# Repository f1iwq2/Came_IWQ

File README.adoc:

Carte CAME-IWQ
==============

Carte de remplacement pour portail coulissants CAME
ZBX6N/7N - A base d'arduino nano
Documents dans le fichier pdf
Fichiers schéma Kicad
fichiers gerber dans le répertoire trace

Replacement control board for CAME sliding gates
Documents in pdf files
Kicad board schematics files
gerber files in trace directory

https://youtu.be/OYu1DCdmt-g

image::clone_came.jpg[]

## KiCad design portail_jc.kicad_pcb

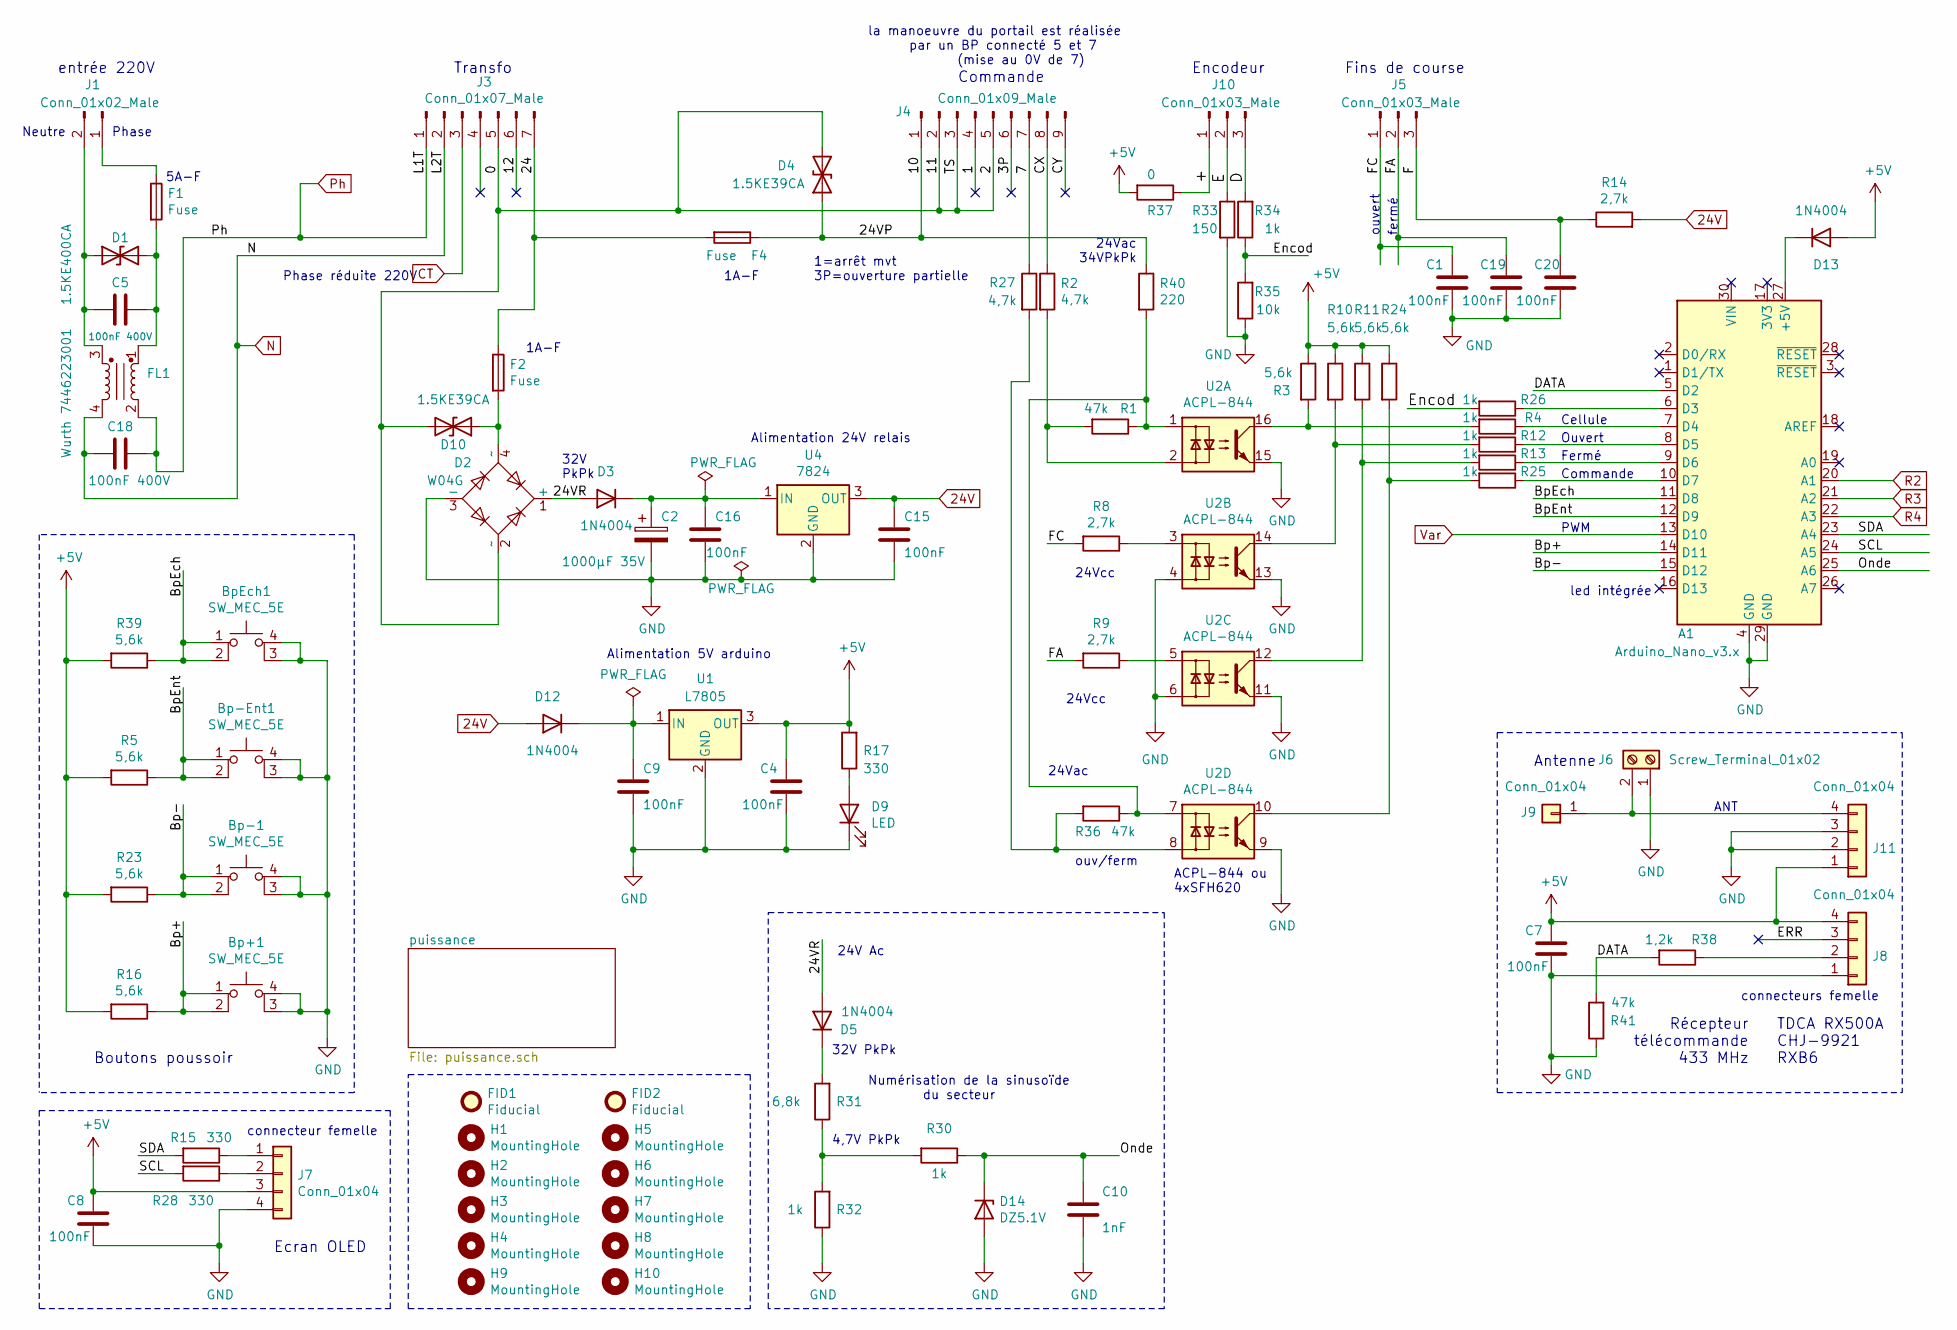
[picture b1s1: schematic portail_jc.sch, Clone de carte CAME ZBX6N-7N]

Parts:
A1: Arduino_Nano_v3.x; Arduino_Nano
Bp+1: SW_MEC_5E; SW_SPST_Omron_B3FS-101xP
Bp-1: SW_MEC_5E; SW_SPST_Omron_B3FS-101xP
Bp-Ent1: SW_MEC_5E; SW_SPST_Omron_B3FS-101xP
BpEch1: SW_MEC_5E; SW_SPST_Omron_B3FS-101xP
C1, C4, C7, C8, C9, C15, C16, C19, C20: 100nF; C_Rect_L7.2mm_W2.5mm_P5.00mm_FKS2_FKP2_MKS2_MKP2
C2: 1000µF 35V; CP_Radial_D12.5mm_P5.00mm
C5, C18: 100nF 400V; C_Rect_L16.5mm_W6.0mm_P15.00mm_MKT
C10: 1nF; C_Rect_L7.2mm_W2.5mm_P5.00mm_FKS2_FKP2_MKS2_MKP2
D1: 1.5KE400CA; R_Axial_DIN0414_L11.9mm_D4.5mm_P15.24mm_Horizontal
D2: W04G; Diode_Bridge_Round_D8.9mm
D3, D5, D12, D13: 1N4004; D_DO-41_SOD81_P10.16mm_Horizontal
D4, D10: 1.5KE39CA; R_Axial_DIN0414_L11.9mm_D4.5mm_P15.24mm_Horizontal
D9: LED; LED_D3.0mm
D14: DZ5.1V; D_A-405_P7.62mm_Horizontal
F1, F2, F4: Fuse; Fuseholder_Cylinder-5x20mm_Schurter_0031_8201_Horizontal_Op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
FID1: Fiducial; KiCad-Logo2_6mm_SilkScreen
FID2: Fiducial; OSHW-Logo2_9.8x8mm_SilkScreen
FL1: Wurth 7446223001; Filtre_wurth
H1, H2, H3, H4: MountingHole; MountingHole_3.2mm_M3
H5, H6, H7, H8: MountingHole; MountingHole_6.4mm_M6
H9, H10: MountingHole; MountingHole_2.7mm_M2.5
J1: Conn_01x02_Male; PhoenixContact_MSTBVA_2,5_2-G-5,08_1x02_P5.08mm_Vertical
J3: Conn_01x07_Male; PhoenixContact_MSTBVA_2,5_7-G-5,08_1x07_P5.08mm_Vertical
J4: Conn_01x09_Male; PhoenixContact_MSTBVA_2,5_9-G-5,08_1x09_P5.08mm_Vertical
J5, J10: Conn_01x03_Male; PhoenixContact_MSTBVA_2,5_3-G-5,08_1x03_P5.08mm_Vertical
J6: Screw_Terminal_01x02; TerminalBlock_bornier-2_P5.08mm
J7, J8, J11: Conn_01x04; PinSocket_1x04_P2.54mm_Vertical
J9: Conn_01x04; PinHeader_1x01_P2.54mm_Vertical
R1, R36, R41: 47k; R_Axial_DIN0207_L6.3mm_D2.5mm_P7.62mm_Horizontal
R2, R27: 4,7k; R_Axial_DIN0207_L6.3mm_D2.5mm_P7.62mm_Horizontal
R3, R5, R10, R11, R16, R23, R24, R39: 5,6k; R_Axial_DIN0207_L6.3mm_D2.5mm_P7.62mm_Horizontal
R4, R12, R13, R25, R26, R30, R32, R34: 1k; R_Axial_DIN0207_L6.3mm_D2.5mm_P7.62mm_Horizontal
R8, R9, R14: 2,7k; R_Axial_DIN0207_L6.3mm_D2.5mm_P7.62mm_Horizontal
R15, R17, R28: 330; R_Axial_DIN0207_L6.3mm_D2.5mm_P7.62mm_Horizontal
R31: 6,8k; R_Axial_DIN0207_L6.3mm_D2.5mm_P7.62mm_Horizontal
R33: 150; R_Axial_DIN0207_L6.3mm_D2.5mm_P7.62mm_Horizontal
R35: 10k; R_Axial_DIN0207_L6.3mm_D2.5mm_P7.62mm_Horizontal
R37: 0; R_Axial_DIN0207_L6.3mm_D2.5mm_P7.62mm_Horizontal
R38: 1,2k; R_Axial_DIN0207_L6.3mm_D2.5mm_P7.62mm_Horizontal
R40: 220; R_Axial_DIN0207_L6.3mm_D2.5mm_P7.62mm_Horizontal
U1: L7805; TO-220-3_Vertical
U2: ACPL-844; DIP-16_W7.62mm_LongPads
U4: 7824; TO-220-3_Vertical

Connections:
24V: C15.1, D12.2 (A), R14.2, U4.3 (OUT); also elsewhere on the board
+5V: C4.1, C7.1, C8.1, D13.2 (A), J7.3, J8.4, J11.1, R3.1, R5.2, R10.1, R11.1, R16.2, R17.2, R23.2, R24.1, R37.2, R39.2, U1.3 (OUT)
/0: D2.2 (~~), D4.2 (A2), D10.2 (A2), J3.5, J4.2, J4.3, J4.5
/1: J4.4
/3P: J4.6
/7: J4.7, R27.1
/10: D4.1 (A1), F4.1, J4.1, R40.1
/12: J3.6
/24: F2.1, F4.2, J3.7
/24VR: D2.1 (+), D3.2 (A), D5.2 (A)
/+: J10.1, R37.1
/Bp+: A1.14 (D11), Bp+1.1, Bp+1.2, R16.1
/Bp-: A1.15 (D12), Bp-1.1, Bp-1.2, R23.1
/BpEch: A1.11 (D8), BpEch1.1, BpEch1.2, R39.1
/BpEnt: A1.12 (D9), Bp-Ent1.1, Bp-Ent1.2, R5.1
/CX: J4.8, R2.1
/CY: J4.9
/D: J10.3, R34.2
/DATA: A1.5 (D2), R38.2, R41.2
/E: J10.2, R33.1
/ERR: J8.3
/Encod: R26.2, R34.1, R35.2
/F: C20.1, J5.3, R14.1
/FA: C19.1, J5.2, R9.2
/FC: C1.1, J5.1, R8.2
/Onde: A1.25 (A6), C10.1, D14.1 (K), R30.1
/SCL: A1.24 (A5), R28.2
/SDA: A1.23 (A4), R15.2
CT: J3.3; also elsewhere on the board
GND: A1.4 (GND), A1.29 (GND), Bp+1.3 (K), Bp+1.4 (A), Bp-1.3 (K), Bp-1.4 (A), Bp-Ent1.3 (K), Bp-Ent1.4 (A), BpEch1.3 (K), BpEch1.4 (A), C1.2, C2.2, C4.2, C7.2, C8.2, C9.2, C10.2, C15.2, C16.2, C19.2, C20.2, D2.3 (-), D9.1 (K), D14.2 (A), J6.1, J7.4, J8.1, J11.2, J11.3, R32.1, R33.2, R35.1, R41.1, U1.2 (GND), U2.4, U2.6, U2.9, U2.11, U2.13, U2.15, U4.2 (GND); also elsewhere on the board
N: C18.2, FL1.4, J3.2; also elsewhere on the board
unnamed: A1.6 (D3), R26.1
unnamed: A1.7 (D4), R4.1
unnamed: A1.8 (D5), R12.1
unnamed: A1.9 (D6), R13.1
unnamed: A1.10 (D7), R25.1
unnamed: A1.27 (+5V), D13.1 (K)
unnamed: C5.1, D1.2 (A2), F1.2, FL1.1
unnamed: C5.2, D1.1 (A1), FL1.3, J1.2
unnamed: C9.1, D12.1 (K), U1.1 (IN)
unnamed: C2.1, C16.1, D3.1 (K), U4.1 (IN)
unnamed: D5.1 (K), R31.2
unnamed: D9.2 (A), R17.1
unnamed: D2.4 (~~), D10.1 (A1), F2.2
unnamed: F1.1, J1.1
unnamed: J7.1, R15.1
unnamed: J7.2, R28.1
unnamed: J8.2, R38.1
unnamed: J6.2, J9.1, J11.4
unnamed: R1.1, R36.1, R40.2, U2.1, U2.7
unnamed: R1.2, R2.2, U2.2
unnamed: R3.2, R4.2, U2.16
unnamed: R8.1, U2.3
unnamed: R9.1, U2.5
unnamed: R10.2, R12.2, U2.14
unnamed: R11.2, R13.2, U2.12
unnamed: R24.2, R25.2, U2.10
unnamed: R27.2, R36.2, U2.8
unnamed: R30.2, R31.1, R32.2
Ph: C18.1, FL1.2, J3.1; also elsewhere on the board
R2: A1.20 (A1); also elsewhere on the board
R3: A1.21 (A2); also elsewhere on the board
R4: A1.22 (A3); also elsewhere on the board
Var: A1.13 (D10); also elsewhere on the board

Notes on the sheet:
entrée 220V
Transfo
Commande
ouv/ferm
Fins de course
Antenne
Ouvert
Fermé
Récepteur télécommande 433 MHz
led intégrée
TDCA RX500A CHJ-9921 RXB6
Ecran OLED
Boutons poussoir
Alimentation 5V arduino
Alimentation 24V relais
Encodeur
Cellule
la manoeuvre du portail est réalisée par un BP connecté 5 et 7 (mise au 0V de 7)
Phase
Neutre
Phase réduite 220V
PWM
32V PkPk
4,7V PkPk
1=arrêt mvt 3P=ouverture partielle
Numérisation de la sinusoïde du secteur
24V Ac
24Vac
24Vcc
24Vac 34VPkPk
1A-F
5A-F
connecteurs femelle
connecteur femelle
fermé
ouvert
ANT
32V PkPk
ACPL-844 ou 4xSFH620

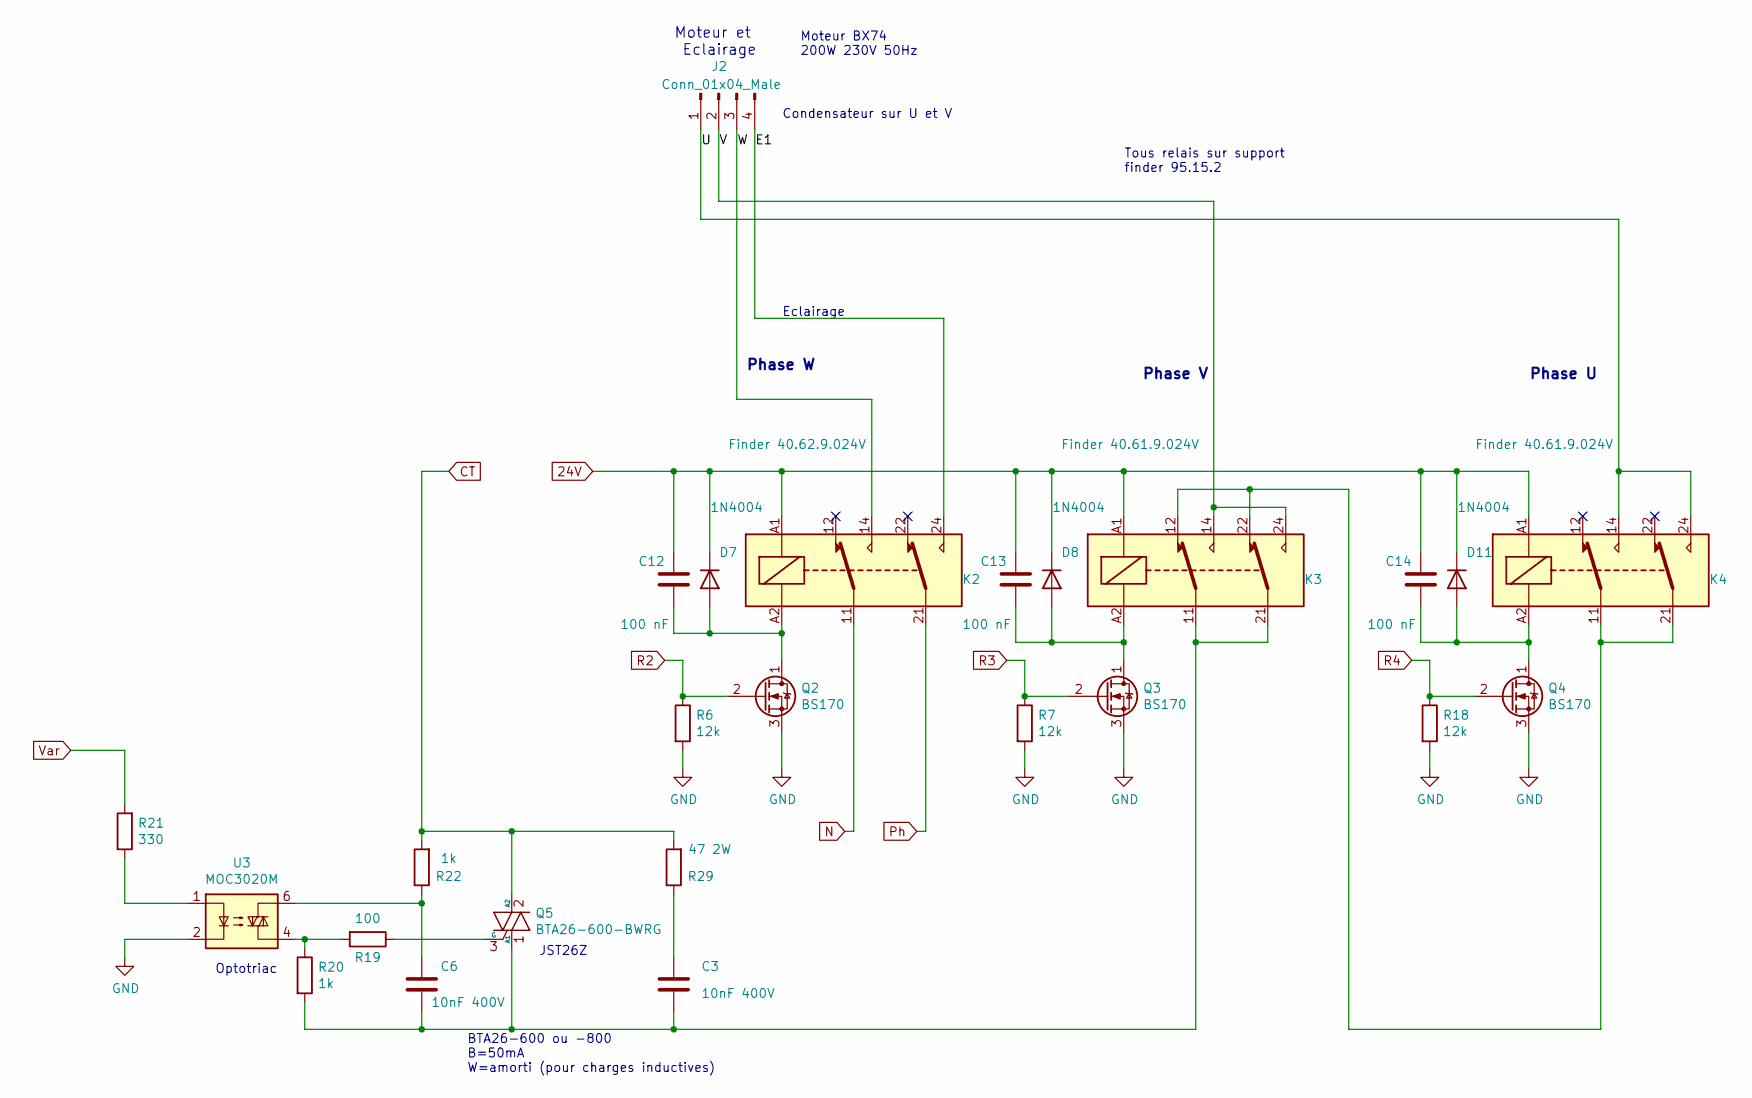
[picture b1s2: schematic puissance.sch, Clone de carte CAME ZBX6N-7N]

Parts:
C3, C6: 10nF 400V; C_Rect_L9.0mm_W2.5mm_P7.50mm_MKT
C12, C13, C14: 100 nF; C_Rect_L7.2mm_W2.5mm_P5.00mm_FKS2_FKP2_MKS2_MKP2
D7, D8, D11: 1N4004; D_DO-41_SOD81_P10.16mm_Horizontal
J2: Conn_01x04_Male; PhoenixContact_MSTBVA_2,5_4-G-5,08_1x04_P5.08mm_Vertical
K2: Finder 40.62.9.024V; Relay_socket_95.15.2
K3, K4: Finder 40.61.9.024V; Relay_socket_95.15.2
Q2, Q3, Q4: BS170; TO-92L_Inline_Wide
Q5: BTA26-600-BWRG; TO-3P-3_Vertical
R6, R7, R18: 12k; R_Axial_DIN0207_L6.3mm_D2.5mm_P7.62mm_Horizontal
R19: 100; R_Axial_DIN0207_L6.3mm_D2.5mm_P7.62mm_Horizontal
R20, R22: 1k; R_Axial_DIN0207_L6.3mm_D2.5mm_P7.62mm_Horizontal
R21: 330; R_Axial_DIN0207_L6.3mm_D2.5mm_P7.62mm_Horizontal
R29: 47 2W; R_Axial_DIN0414_L11.9mm_D4.5mm_P15.24mm_Horizontal
U3: MOC3020M; DIP-6_W7.62mm_LongPads

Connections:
24V: C12.1, C13.1, C14.1, D7.1 (K), D8.1 (K), D11.1 (K), K2.A1, K3.A1, K4.A1; also elsewhere on the board
/puissance/E1: J2.4, K2.24
/puissance/U: J2.1, K4.14, K4.24
/puissance/V: J2.2, K3.14, K3.24
/puissance/W: J2.3, K2.14
CT: Q5.2 (A2), R22.2, R29.2; also elsewhere on the board
GND: Q2.3 (S), Q3.3 (S), Q4.3 (S), R6.2, R7.2, R18.2, U3.2; also elsewhere on the board
N: K2.11; also elsewhere on the board
unnamed: C3.1, R29.1
unnamed: C3.2, C6.2, K3.11, K3.21, Q5.1 (A1), R20.2
unnamed: C6.1, R22.1, U3.6
unnamed: C12.2, D7.2 (A), K2.A2, Q2.1 (D)
unnamed: C13.2, D8.2 (A), K3.A2, Q3.1 (D)
unnamed: C14.2, D11.2 (A), K4.A2, Q4.1 (D)
unnamed: K3.12, K3.22, K4.11, K4.21
unnamed: Q5.3 (G), R19.1
unnamed: R19.2, R20.1, U3.4
unnamed: R21.1, U3.1
Ph: K2.21; also elsewhere on the board
R2: Q2.2 (G), R6.1; also elsewhere on the board
R3: Q3.2 (G), R7.1; also elsewhere on the board
R4: Q4.2 (G), R18.1; also elsewhere on the board
Var: R21.2; also elsewhere on the board

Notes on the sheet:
Tous relais sur support finder 95.15.2
Moteur et Eclairage
Optotriac
Phase V
Phase U
Phase W
Eclairage
Condensateur sur U et V
JST26Z
Moteur BX74 200W 230V 50Hz
BTA26-600 ou -800 B=50mA W=amorti (pour charges inductives)

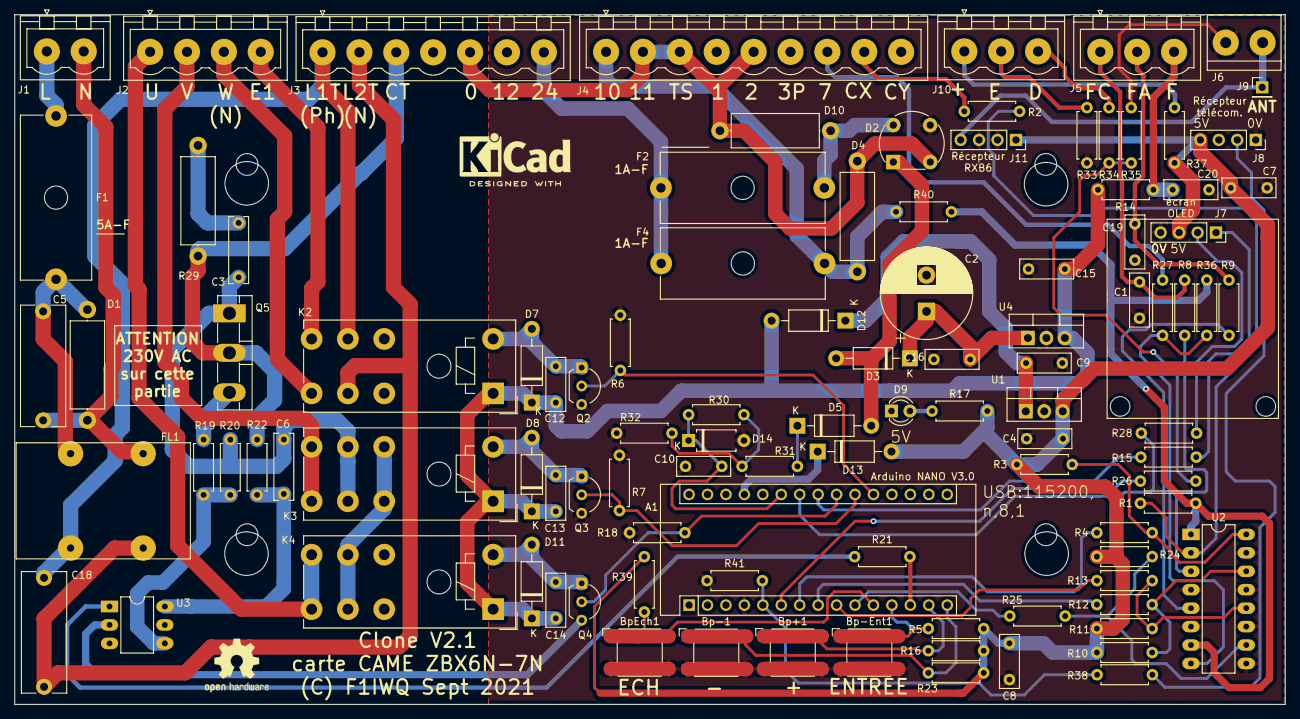
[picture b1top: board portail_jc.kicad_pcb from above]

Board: 2 copper layers, 175.0 x 95.0 mm, 115 parts (0 on the bottom side), 73 nets.

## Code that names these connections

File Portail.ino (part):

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// L'origine 0 de l'encodeur est en position reculée (Fc arrière)=portail ouvert
// *********************************************************
// Compilation pour la carte V1.0 ou V2.0
// en V1 : l'encodeur est traité par l'IRQ matérielle, encod sur pin D8.
// ----------------------------------------------------------------------------------
// en V2 : l'encodeur est traité par l'IRQ matérielle, encod sur pin D3
// ----------------------------------------------------------------------------------
// 1 tour programme principal (main) dure en moyenne 800 à 850µs
//
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#define   led       13     // D13 portB.5 led intégrée
#define   BpM       12     // D12 portB.4 Bouton -
#define   BpP       11     // D11 portB.3 Bouton +
#define   Var       10     // D10 portB.2 Variation (commande triac)
#define   BpE        9     // D9  portB.1 Bouton ENTREE
#define   Commande   7     // D7  portD.7 ommande ouverture/fermeture 
#define   FcFerme    6     // D6  portD.6 Fin de course fermé
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#define   data       2     // D2  portD.2 Rx radio 433 MHz

#ifdef    V1               // définitions spécifiques de la carte V1
#define   encod      8     // D8  portB.0 Encodeur 
#define   BpEch      3     // D3  portD.3 Bouton Ech
#endif

#ifdef    V2               // définitions spécifiques de la carte V2
#define   encod      3     // D3  portD.3 Encodeur 
#define   BpEch      8     // D8  portB.0 Bouton Ech
#endif

// port C de l'ATMEGA328 
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#define   R2        A1     // portC.1 bit 1 Relais 2
#define   Tick      A0     // portC.0 bit 0 tour programme debug oscilloscope
// A6 et A7 uniquement en entrée analogiques - 10 bits valeurs de 0 à 1023.
#define   Onde      6     // A6 numérisation signal secteur 
#define   rien      7     // A7

#define   Nbre_Max_telecom 20  // nombre maxi de télécommandes 
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      compteur_ech=0;
    }
  
    // pilotage de la pin VAR à 1 si pas arrêté
    if ( !arrete & (compteur_ech>=angle_retard) & (compteur_ech<angle_retard+10) & // +10 détermine la largeur du créneau envoyé à la gachette
         ( 
            m1 | 
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  pinMode(R2,OUTPUT); digitalWrite(R2,LOW);
  pinMode(R3,OUTPUT); digitalWrite(R3,LOW);
  pinMode(R4,OUTPUT); digitalWrite(R4,LOW);
  pinMode(Var,OUTPUT);digitalWrite(Var,LOW);
  pinMode(led,OUTPUT);
  pinMode(Tick,OUTPUT);

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  pinMode(FcFerme,INPUT);
  pinMode(FcOuvert,INPUT);
  pinMode(Cellule,INPUT);
  pinMode(encod,INPUT);
  pinMode(BpP,INPUT);
  pinMode(BpM,INPUT);
  pinMode(BpE,INPUT);
  pinMode(BpEch,INPUT);
  pinMode(data,INPUT);
  
  Serial.println(F("Programme portail JC - F1IWQ 2022\r\nTapez ? pour l'aide"));
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  
  #ifdef V2
  //en V2 association de l'IRQ INT1 sur portB.D3=encodeur
  attachInterrupt(digitalPinToInterrupt(encod),gest_encodeur,CHANGE);
  #endif
  
  // Initialisation des variables
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
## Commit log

2021-08-30 V2.0
2021-08-31 V2.1
2021-09-07 V2.2
2021-09-10 V2.3
2021-09-10 V2.31
2021-09-12 V2.32
2021-09-13 V2.33
2021-09-13 V2.34
2021-09-13 prog
2021-09-13 V2.35
2021-09-14 2.36
2021-09-15 V2.37
2021-09-15 V2.38
2021-09-16 V2.39
2021-09-16 V2.40
2021-09-17 V2.41
2021-09-22 V2.42
2021-09-25 2.43
2021-11-30 improve program
2021-12-03 update prog & doc
2021-12-04 Update 2
2021-12-04 update 3
2022-06-24 soft update & schema
2022-07-02 Update software (portail.ino)
2022-07-10 Update software
2022-10-01 Softwate update 1 oct 2022
